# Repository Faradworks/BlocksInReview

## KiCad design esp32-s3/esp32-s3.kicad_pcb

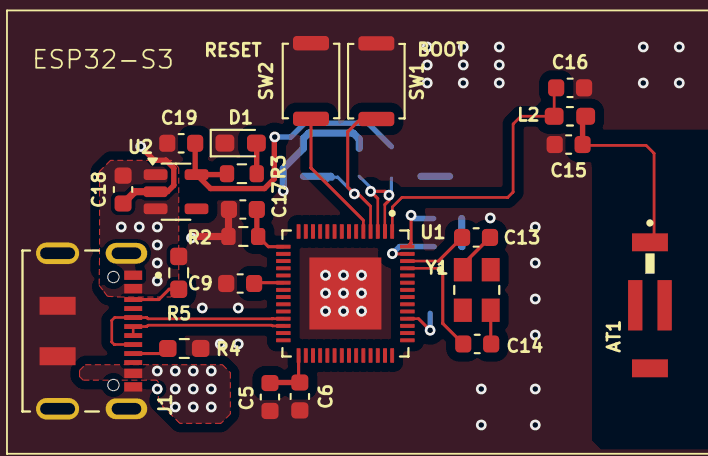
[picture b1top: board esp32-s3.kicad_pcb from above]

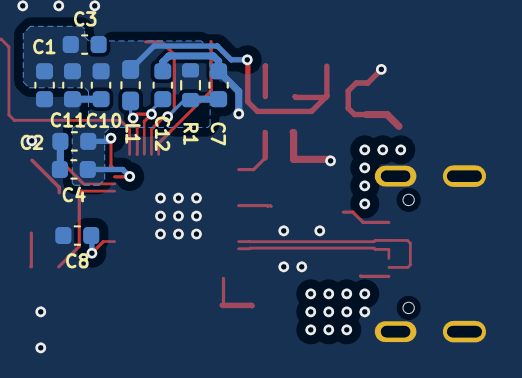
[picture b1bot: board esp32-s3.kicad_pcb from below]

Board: 4 copper layers, 34 parts (11 on the bottom side), 21 nets.

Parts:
AT1: 2450AT43B100E; ANTENNA_2450AT43B100E
C1, C4, C5, C7, C8, C9, C10, C16, C17: 1uF; C_0603_1608Metric
C2, C6, C11, C12, C15: 0.1uF; C_0603_1608Metric
C3, C18, C19: 22uF; C_0603_1608Metric
C13, C14: 16pF; C_0603_1608Metric
D1: LED; LED_0603_1608Metric_Pad1.05x0.95mm_HandSolder
J1: DX07S016JA1R1500; JAE_DX07S016JA1R1500
L1: GZ2012D601TF; L_0603_1608Metric_Pad1.05x0.95mm_HandSolder
L2: 2.2nH; L_0603_1608Metric_Pad1.05x0.95mm_HandSolder
R1: 10k; R_0603_1608Metric
R2: 1M; R_0603_1608Metric
R3: 4.7K; R_0603_1608Metric
R4, R5: 5.1K; R_0603_1608Metric_Pad0.98x0.95mm_HandSolder
SW1: RESET; SW_Push_SPST_NO_Alps_SKRK
SW2: BOOT; SW_Push_SPST_NO_Alps_SKRK
U1: ESP32-S3FN8; QFN40P700X700X90-57N
U2: AP2112K-3.3; SOT-23-5
Y1: 40Mhz; XTAL_SXT32412CC38-40.000MT

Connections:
/ESP32-S3/3V3: C1.1, C2.1, C3.1, C4.1, C10.1, C11.1, C19.1, L1.2, R1.1, R3.1, U1.55 (VDDA1), U1.56 (VDDA2), U2.5 (VOUT)
/ESP32-S3/D+: J1.6 (D+), J1.7 (D+), U1.26 (GPIO20)
/ESP32-S3/D-: J1.5 (D-), J1.8 (D-), U1.25 (GPIO19)
/ESP32-S3/GND: C1.2, C2.2, C3.2, C4.2, C5.1, C6.2, C7.1, C8.2, C9.2, C10.2, C11.2, C12.2, C15.2, C16.2, C17.2, C18.2, C19.2, D1.1 (K), J1.1 (GND), J1.12 (GND), J1.S1 (SHIELD), J1.S2 (SHIELD), J1.S3 (SHIELD), J1.S4 (SHIELD), J1.S5 (SHIELD), J1.S6 (SHIELD), R2.2, R4.2, R5.1, SW1.1, SW2.2, U1.57 (GND), U2.2 (GND)
/ESP32-S3/GPIO10_DBLTAP: C17.1, R2.1, U1.15 (GPIO10)
/ESP32-S3/LNA_IN: C16.1, L2.2, U1.1 (LNA_IN)
/ESP32-S3/VBUS: C18.1, J1.2 (VBUS), J1.11 (VBUS), U2.1 (VIN), U2.3 (EN)
/ESP32-S3/VDD3P3: C12.1, L1.1, U1.2 (VDD3P3), U1.3 (VDD3P3)
/ESP32-S3/VDD3P3_CPU: C8.1, U1.46 (VDD3P3_CPU)
/ESP32-S3/VDD3P3_RTC: C9.1, U1.20 (VDD3P3_RTC)
/ESP32-S3/VDD_SPI: C5.2, C6.1, U1.29 (VDD_SPI)
unnamed: AT1.1, C15.1, L2.1
unnamed: C13.1, Y1.1
unnamed: C14.1, Y1.3
unnamed: D1.2 (A), R3.2
unnamed: J1.3 (CC1), R5.2
unnamed: J1.9 (CC2), R4.1
unnamed: C7.2, R1.2, SW1.2, U1.4 (CHIP_PU)
unnamed: SW2.1, U1.5 (GPIO0)
unnamed: C14.2, U1.53 (XTAL_N)
unnamed: C13.2, U1.54 (XTAL_P)

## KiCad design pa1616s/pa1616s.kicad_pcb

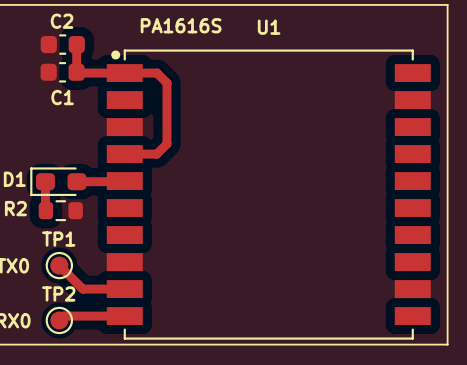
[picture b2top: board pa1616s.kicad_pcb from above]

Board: 4 copper layers, 7 parts (0 on the bottom side), 6 nets.

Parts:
C1: 10uF; C_0603_1608Metric
C2: 0.1uF; C_0603_1608Metric
D1: LED; LED_0603_1608Metric_Pad1.05x0.95mm_HandSolder
R2: 4.7K; R_0603_1608Metric
TP1: TX0; TestPoint_Pad_D1.0mm
TP2: RX0; TestPoint_Pad_D1.0mm
U1: PA1616S

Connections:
/PA1616S/GND: C1.2, C2.2, R2.2, U1.3 (GND), U1.8 (GND), U1.12 (GND), U1.19 (GND)
/PA1616S/RX0: TP2.1, U1.10 (RX0)
/PA1616S/TX0: TP1.1, U1.9 (TX0)
/PA1616S/VCC: C1.1, C2.1, U1.1 (VCC), U1.4 (VBACKUP)
unnamed: D1.2 (A), U1.5 (3D-FIX)
unnamed: D1.1 (K), R2.1

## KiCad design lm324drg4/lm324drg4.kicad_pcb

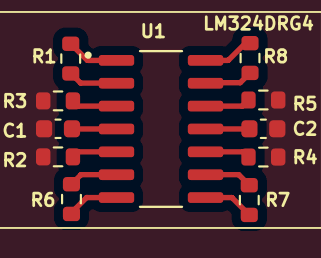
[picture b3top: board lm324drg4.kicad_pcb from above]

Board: 4 copper layers, 11 parts (0 on the bottom side), 15 nets.

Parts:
C1, C2: 0.1uF; C_0603_1608Metric
R1, R2, R3, R4, R5, R6, R7, R8: 100k; R_0603_1608Metric
U1: LM324DRG4; SOIC127P600X175-14N

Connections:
/LM324DRG4/GND: C1.2, C2.2, R2.1, R3.1, R4.1, R5.1
/LM324DRG4/OUT1: R1.1, U1.1 (1OUT)
/LM324DRG4/OUT2: R6.1, U1.7 (2OUT)
/LM324DRG4/OUT3: R7.1, U1.8 (3OUT)
/LM324DRG4/OUT4: R8.1, U1.14 (4OUT)
/LM324DRG4/PD0: R1.2, U1.2 (1IN-)
/LM324DRG4/PD1: R6.2, U1.6 (2IN-)
/LM324DRG4/PD2: R7.2, U1.9 (3IN-)
/LM324DRG4/PD3: R8.2, U1.13 (4IN-)
/LM324DRG4/VCC: C1.1, U1.4 (VCC)
/LM324DRG4/VEE: C2.1, U1.11 (GND)
unnamed: R3.2, U1.3 (1IN+)
unnamed: R2.2, U1.5 (2IN+)
unnamed: R4.2, U1.10 (3IN+)
unnamed: R5.2, U1.12 (4IN+)

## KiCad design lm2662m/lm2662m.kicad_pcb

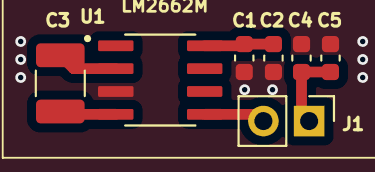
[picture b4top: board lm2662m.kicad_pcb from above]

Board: 4 copper layers, 7 parts (0 on the bottom side), 6 nets.

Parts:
C1, C4: 10uF; C_0603_1608Metric
C2, C5: 0.1uF; C_0603_1608Metric
C3: 47uF; C_1210_3225Metric_Pad1.33x2.70mm_HandSolder
J1: Jumper; PinHeader_1x02_P2.54mm_Vertical
U1: LM2662M; SOIC127P599X175-8N

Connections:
/LM2662M/GND: C1.2, C2.2, C4.2, C5.2, U1.3 (GND)
/LM2662M/VCC: C1.1, C2.1, U1.8 (V+)
/LM2662M/VEE: C4.1, C5.1, J1.1
unnamed: J1.2, U1.5 (OUT)
unnamed: C3.1, U1.2 (CAP+)
unnamed: C3.2, U1.4 (CAP-)

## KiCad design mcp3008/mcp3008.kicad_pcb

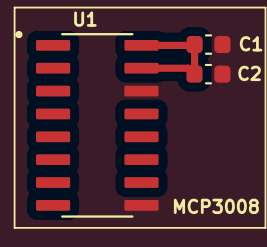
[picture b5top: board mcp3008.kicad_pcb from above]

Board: 4 copper layers, 3 parts (0 on the bottom side), 2 nets.

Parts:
C1: 1uF; C_0603_1608Metric
C2: 0.1uF; C_0603_1608Metric
U1: MCP3008; SOIC127P600X175-16N

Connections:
/MCP3008/GND: C1.2, C2.2, U1.9 (DGND), U1.14 (AGND)
/MCP3008/VDD: C1.1, C2.1, U1.15 (Vref), U1.16 (Vdd)

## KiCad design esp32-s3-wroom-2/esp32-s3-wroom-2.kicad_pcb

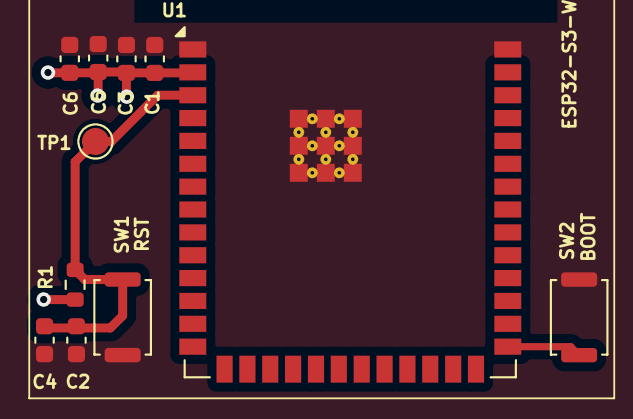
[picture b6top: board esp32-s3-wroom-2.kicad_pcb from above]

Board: 4 copper layers, 11 parts (0 on the bottom side), 4 nets.

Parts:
C1: 22uF; C_0603_1608Metric
C2: 1uF; C_0603_1608Metric
C3, C4, C5, C6: 0.1uF; C_0603_1608Metric
R1: 10k; R_0603_1608Metric
SW1: RST; SW_Push_SPST_NO_Alps_SKRK
SW2: BOOT; SW_Push_SPST_NO_Alps_SKRK
TP1: T_EN; TestPoint_Pad_D1.5mm
U1: ESP32-S3-WROOM-2

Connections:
/esp32-s3-wroom-2/3V3: C1.1, C3.1, C5.1, C6.1, R1.1, U1.2 (3V3)
/esp32-s3-wroom-2/GND: C1.2, C2.2, C3.2, C4.2, C5.2, C6.2, SW1.1, SW2.2, U1.1 (GND), U1.40 (GND), U1.41 (GND)
unnamed: C2.1, C4.1, R1.2, SW1.2, TP1.1, U1.3 (EN)
unnamed: SW2.1, U1.27 (IO0)

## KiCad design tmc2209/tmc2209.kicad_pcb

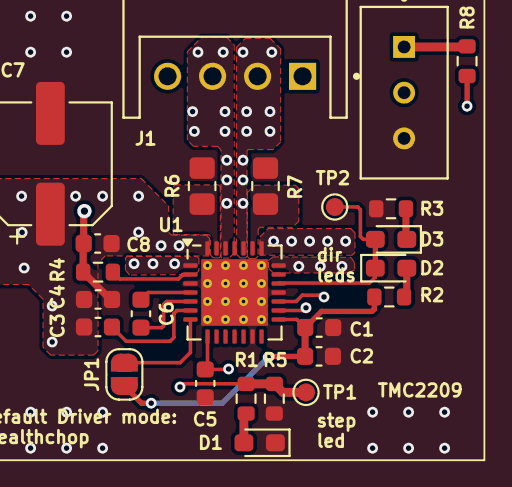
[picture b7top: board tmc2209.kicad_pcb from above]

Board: 4 copper layers, 25 parts (0 on the bottom side), 22 nets.

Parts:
C1, C5: 10uF; C_0603_1608Metric
C2, C3, C4, C8: 0.22uF; C_0603_1608Metric
C6: 22nF; C_0603_1608Metric
C7: 22uF; CP_Elec_6.3x5.4
D1, D2, D3: LED; LED_0603_1608Metric_Pad1.05x0.95mm_HandSolder
J1: MOTOR CONNECTOR; JST_S4B-XH-A_LF__SN_
JP1: MOTOR DRIVER MODE; SolderJumper-2_P1.3mm_Open_RoundedPad1.0x1.5mm
R1, R4: 20K; R_0603_1608Metric
R2, R3: 4.7K; R_0603_1608Metric
R5: 2.2K; R_0603_1608Metric
R6, R7: 0.05R; R_0805_2012Metric_Pad1.20x1.40mm_HandSolder
R8: 33K; R_0603_1608Metric
RV1: 10K; TRIM_3296W1103LF
TP1: STEP; TestPoint_Pad_D1.0mm
TP2: DIR; TestPoint_Pad_D1.0mm
U1: TMC2209-LA; VQFN-28-1EP_5x5mm_P0.5mm_EP3.7x3.7mm_ThermalVias

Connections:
/TMC2209/5VOUT: C5.1, R8.1, U1.8 (5VOUT)
/TMC2209/DIR: D2.1 (K), D3.2 (A), TP2.1, U1.19 (DIR)
/TMC2209/GND: C1.2, C2.2, C4.2, C5.2, C7.2, C8.2, D1.1 (K), R3.2, R4.2, R5.2, R6.2, R7.2, RV1.3, U1.3 (GND), U1.13 (CLK), U1.18 (GND), U1.29 (GND)
/TMC2209/OUT1A: J1.2, U1.24 (OA1)
/TMC2209/OUT1B: J1.3, U1.26 (OB1)
/TMC2209/OUT2A: J1.1, U1.21 (OA2)
/TMC2209/OUT2B: J1.4, U1.1 (OB2)
/TMC2209/STEP: R1.1, R5.1, TP1.1, U1.16 (STEP)
/TMC2209/VCC_IO: C1.1, C2.1, JP1.1 (A), R2.1, U1.15 (VCC_IO)
/TMC2209/VMOTOR: C3.1, C4.1, C7.1, C8.1, U1.22 (VS), U1.28 (VS)
unnamed: D1.2 (A), R1.2
unnamed: D2.2 (A), R2.2
unnamed: D3.1 (K), R3.1
unnamed: JP1.2 (B), U1.7 (SPREAD)
unnamed: R8.2, RV1.1
unnamed: R7.1, U1.23 (BRA)
unnamed: R6.1, U1.27 (BRB)
unnamed: C6.2, U1.5 (CPI)
unnamed: C6.1, U1.4 (CPO)
unnamed: C3.2, U1.6 (VCP)
unnamed: RV1.2, U1.17 (VREF)
unnamed: R4.1, U1.2 (~EN)

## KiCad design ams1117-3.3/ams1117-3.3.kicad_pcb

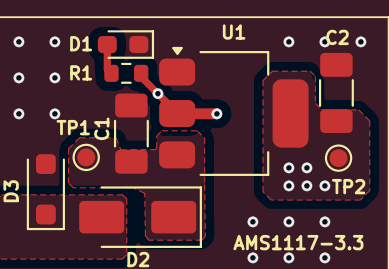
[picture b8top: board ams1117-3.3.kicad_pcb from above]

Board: 4 copper layers, 9 parts (0 on the bottom side), 5 nets.

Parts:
C1, C2: 22uF; C_1206_3216Metric_Pad1.33x1.80mm_HandSolder
D1: LED; LED_0603_1608Metric_Pad1.05x0.95mm_HandSolder
D2: SS14; D_SMA
D3: SMF12A; D_SOD-123F
R1: 4.7K; R_0603_1608Metric
TP1: VIN; TestPoint_Pad_D1.0mm
TP2: 3V3; TestPoint_Pad_D1.0mm
U1: AMS1117-3.3; SOT-223-3_TabPin2

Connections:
/block_ams1117-3.3/+3V3: C2.1, R1.1, TP2.1, U1.2 (VO)
/block_ams1117-3.3/GND: C1.2, C2.2, D1.1 (K), D3.2 (A2), U1.1 (GND)
/block_ams1117-3.3/VIN: D2.2 (A), D3.1 (A1)
unnamed: D1.2 (A), R1.2
unnamed: C1.1, D2.1 (K), TP1.1, U1.3 (VI)

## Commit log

2025-06-02 [Rushil] created circuit block for MCP9808
2025-06-03 [Rushil] added user drwaing for block outline, removed test point, reduced the size of block and solved white space issue
2025-06-03 [Rushil] removed mos, made more compact, designator resize according to constraints,default id on silk screen
2025-06-04 [Rushil] address on silkscreen corrected and removed on pad vias
2025-06-05 [Rushil] created circuit block of bme680
2025-06-05 [Rushil] added default id on skillscreen
2025-06-05 [Rushil] added step file of D1, clean symbol field added default addr
2025-06-05 [Rushil] edited mcp9808 json with respect to the corrected ciruit
2025-06-07 [Rushil] created block for esp32-s3-wroom-2
2025-06-07 [Rushil] added block for bno055
2025-06-07 [Rushil] added block of ds3231_rtc
2025-06-08 [Rushil] corrected pcb added information on both schematic and pcb user drawing correct circuit of bno055
2025-06-08 [Rushil] added micro_sd block
2025-06-08 [Rushil] small change
2025-06-08 [Rushil] small change in pcb
2025-06-09 [Rushil] added ams1117-3.3 block and did some clean up in schematic info part
2025-06-09 [Rushil] did some clean up
2025-06-10 Edited and finalized blocks MCP9809 and DS3231
2025-06-10 fixed BNO055
2025-06-10 finalized BNO055
2025-06-10 bug fixes in BME680
2025-06-10 fixed microsd
2025-06-10 finalised AMS1117
2025-06-12 [Rushil] add tmc2209 block
2025-06-13 [Rushil] added some more info on silkscreen
2025-06-13 [Rushil] fixed block name of esp32 wroom
2025-06-13 [Rushil] fixed block esp32 wroom
2025-06-13 [Rushil] fixed block esp32 wroom json
2025-06-13 [Rushil] small changes in esp32 wroom
2025-06-15 [Rushil] added mcp3008 circuit block
2025-06-15 [Rushil] added LM324DRG4 circuit block
2025-06-15 [Rushil] added lm2662 circuit block
2025-06-16 [Rushil] changed vccn to vee
2025-06-17 [Rushil] added pa1616s circuit block
2025-06-17 [Rushil] pa1616s
2025-06-22 [Rushil] added esp32-s3 circuit block with usb
2025-06-29 [Rushil] added ldo
2025-06-29 [Rushil] some minor changes
